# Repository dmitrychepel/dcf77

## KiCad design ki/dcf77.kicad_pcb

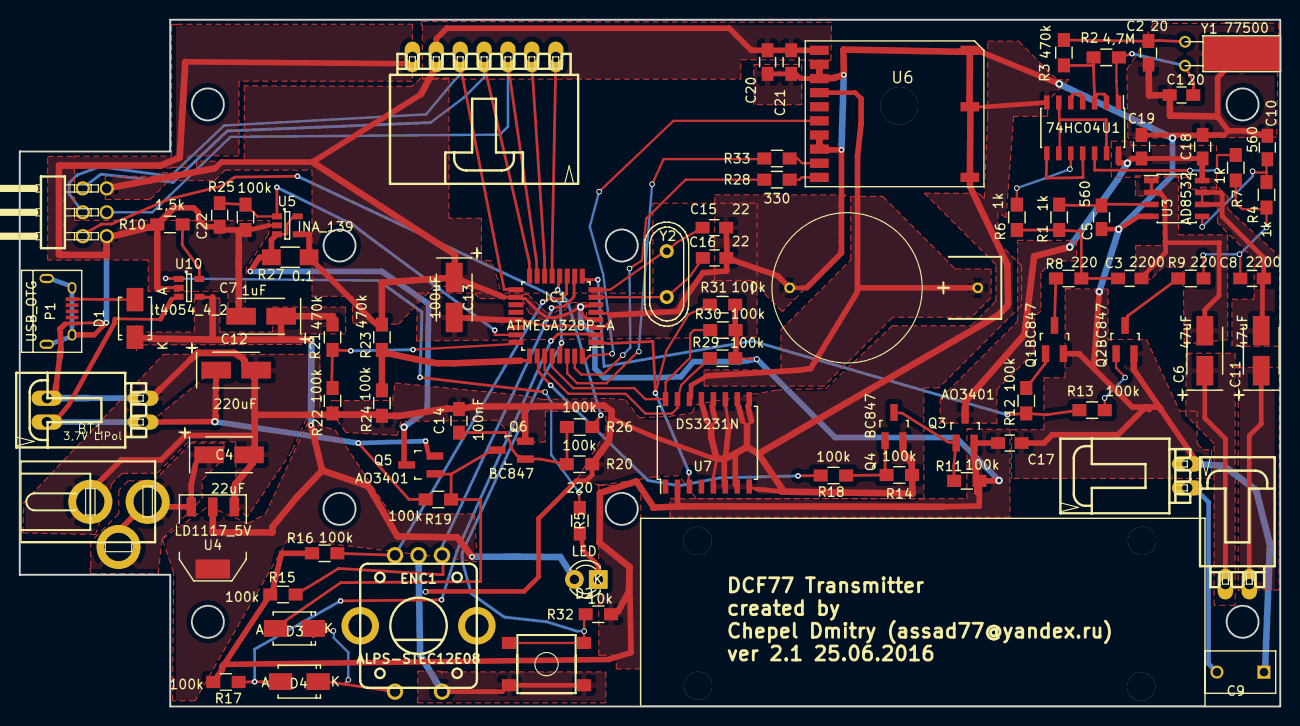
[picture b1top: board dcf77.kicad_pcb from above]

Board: 2 copper layers, 134.0 x 73.0 mm, 86 parts (1 on the bottom side), 63 nets.

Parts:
BT1: 3,7V LiPol; con-molex-70553-02
C1, C2: 20; C_0805_HandSoldering
C3, C8: 2200; C_0805_HandSoldering
C4: 22uF; TantalC_SizeB_EIA-3528_HandSoldering
C5, C10: 560; C_0805_HandSoldering
C6, C11: 47uF; TantalC_SizeB_EIA-3528_HandSoldering
C7: 1uF; TantalC_SizeB_EIA-3528_HandSoldering
C9: 680pF; C_Disc_D7.5_P5
C12: 220uF; TantalC_SizeB_EIA-3528_HandSoldering
C13: 100uF; TantalC_SizeB_EIA-3528_HandSoldering
C14: 100nF; C_0805_HandSoldering
C15, C16: 22; C_0805_HandSoldering
C17, C22: 10uF; C_0805_HandSoldering
C18, C19: 4,7uF; C_0805_HandSoldering
C20: 1uF; C_0805_HandSoldering
C21: 0,1uF; C_0805_HandSoldering
CON1: AVR-ISP-6; atmel-1-AVR-ISP-6R
D1: D_Schottky; SMA_Standard
D2: LED; LED-3MM
D3, D4: D; SMA_Standard
ENC1: ALPS-STEC12E08
IC1: ATMEGA328P-A; TQFP-32_7x7mm_Pitch0.8mm
J1: JACK_2P; con-jack-DCJ0303
L1: 6mH; con-molex-70553-02
L2: 25 circles; con-molex-70553-02-real
P1: USB_OTG; USB_Micro-B
P2: CONN_BAT_EXT; con-molex-70553-02-real
P4: CONN_01X07; con-molex-70553-07
Q1, Q2, Q4, Q6: BC847; SOT-23_Handsoldering
Q3, Q5: AO3401; SOT-23_Handsoldering
R1, R4, R6, R7: 1k; R_0805_HandSoldering
R2: 4,7M; R_0805_HandSoldering
R3, R21, R23: 470k; R_0805_HandSoldering
R5, R8, R9: 220; R_0805_HandSoldering
R10: 1,5k; R_0805_HandSoldering
R11, R12, R13, R14, R15, R16, R17, R18, R19, R20, R22, R24, R25, R26, R29, R30, R31: 100k; R_0805_HandSoldering
R27: 0.1; R_1206_HandSoldering
R28, R33: 330; R_0805_HandSoldering
R32: 10k; R_0805_HandSoldering
SW1: Switch_DPST; switch-tact-DTSM-6-rot
U1: 74HC04; SOIC-14_3.9x8.7mm_Pitch1.27mm
U2: 3,7 V; sn2032-SN2032
U3: AD8532; SOIC-8_3.9x4.9mm_Pitch1.27mm
U4: LD1117_5V; SOT-223
U5: INA_139; SOT-23-5
U6: FGPMMOPA6C; FFGPMMOPA6C
U7: DS3231N; SOIC-16_7.5x10.3mm_Pitch1.27mm
U10: lt4054_4_2; SOT-23-5
Y1: 77500; Crystal_Watch
Y2: 8MHz; Crystal_HC49-U_Vertical

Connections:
/CLOCK: CON1.3, IC1.17, P4.5
/INPUT: IC1.25, R23.2, R24.1
/LED_CS: IC1.14, P4.2
/LED_DC: IC1.13, P4.1
/MISO: CON1.1, IC1.16, P4.4
/MOSI: CON1.4, IC1.15, P4.3
/PPS: IC1.32, U6.6
/ROT1: ENC1.A, IC1.10, R15.1
/ROT2: ENC1.B, IC1.11, R16.1
/RX: R28.1, U6.10
/R_BTN: D4.2, IC1.2, R17.1
/SDA: IC1.27, R29.2, U7.15
/SDL: IC1.28, R30.2, U7.16
/SQW: IC1.1, R31.2, U7.3
/TX: R33.1, U6.9
/VOLTAGE: IC1.24, R21.2, R22.1
CURRENT: C22.1, IC1.23, R25.1, U5.1
GND: BT1.2, C1.2, C2.2, C4.2, C5.2, C7.2, C9.1, C10.2, C12.2, C13.2, C14.2, C15.1, C16.2, C17.2, C18.2, C19.2, C20.2, C21.2, C22.2, CON1.6, ENC1.C, ENC1.SW1, IC1.3, IC1.5, IC1.21, J1.3, L1.2, P1.5, P1.6, P2.2, P4.7, Q1.2, Q2.2, Q4.2, Q6.2, R10.2, R14.2, R20.2, R22.2, R24.2, R25.2, SW1.1, SW1.3, U1.7, U2.2, U3.4, U4.1, U5.2, U6.2, U6.3, U6.7, U6.8, U6.11, U6.12, U6.13, U7.5, U7.6, U7.7, U7.8, U7.9, U7.10, U7.11, U7.12, U7.13, U10.2
unnamed: BT1.1, C12.1, P2.1, Q5.2, R19.2, U10.3
unnamed: C1.1, R2.2, U1.1, Y1.1
unnamed: C2.1, R3.2, Y1.2
unnamed: C3.1, R1.2, R6.1, R8.2
unnamed: C3.2, C6.2, U3.1, U3.2
unnamed: C4.1, J1.1, J1.2, U4.3
unnamed: C5.1, R1.1, U3.3
unnamed: C6.1, L2.1
unnamed: C8.1, R4.2, R7.1, R9.2
unnamed: C9.2, L1.1
unnamed: C10.1, R4.1, U3.5
unnamed: C11.1, L2.2
unnamed: C8.2, C11.2, U3.6, U3.7
unnamed: C14.1, Q6.1, R20.1, R26.2
unnamed: C15.2, IC1.8, Y2.1
unnamed: C16.1, IC1.7, Y2.2
unnamed: CON1.5, IC1.29, R32.2, SW1.2, SW1.4
unnamed: D1.2, P1.1
unnamed: D2.1, R5.2
unnamed: D3.1, D4.1, ENC1.SW2
unnamed: IC1.9, R12.1, R13.1
unnamed: IC1.30, R33.2
unnamed: IC1.31, R28.2
unnamed: Q1.1, R12.2
unnamed: Q1.3, R8.1
unnamed: Q2.1, R13.2
unnamed: Q2.3, R9.1
unnamed: Q3.1, Q4.3, R11.1
unnamed: Q4.1, R14.1, R18.2
unnamed: Q5.3, R27.2, U5.3, U5.5
unnamed: R2.1, R3.1, U1.2, U1.3
unnamed: R5.1, U10.1
unnamed: R6.2, U1.10
unnamed: R7.2, U1.12
unnamed: R10.1, U10.5
unnamed: U1.4, U1.5
unnamed: U1.8, U1.11
unnamed: U1.6, U1.9, U1.13
ON_BTN: D3.2, Q5.1, Q6.3, R19.1
PWR_ON: IC1.12, R26.1
RADIO_ON: IC1.26, R18.1
VAA: C7.1, D1.1, D2.2, R21.1, U4.2, U10.4
VCC: C13.1, C17.1, C20.1, C21.1, CON1.2, IC1.4, IC1.6, IC1.18, P4.6, Q3.2, R11.2, R15.2, R16.2, R17.2, R23.1, R27.1, R29.1, R30.1, R31.1, R32.1, U5.4, U6.1, U7.2
VDD: C18.1, C19.1, Q3.3, U1.14, U3.8
VEE: U2.1, U6.4, U7.14

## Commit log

2017-12-01 init commit
